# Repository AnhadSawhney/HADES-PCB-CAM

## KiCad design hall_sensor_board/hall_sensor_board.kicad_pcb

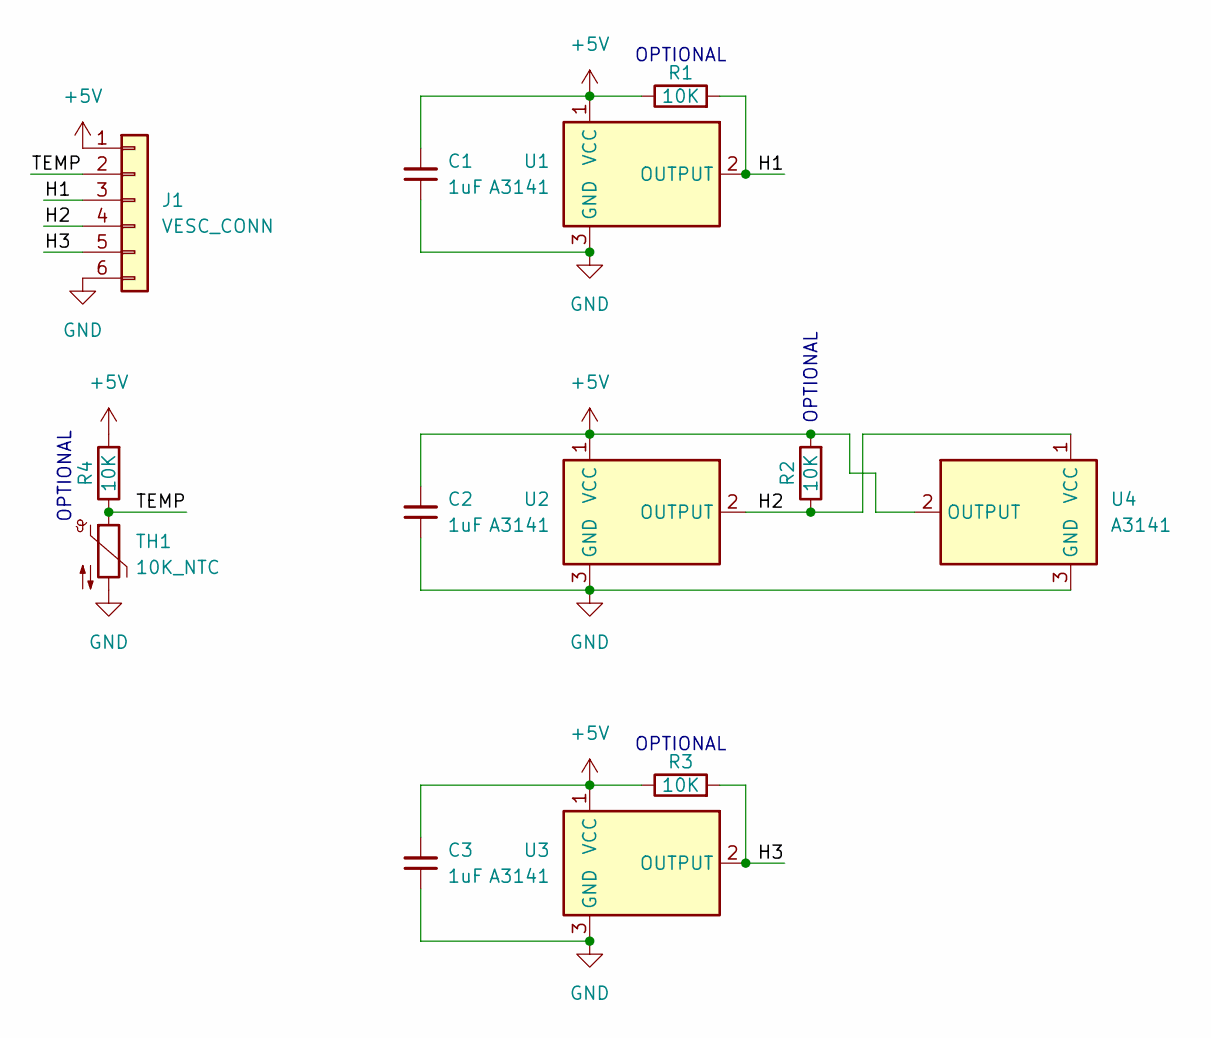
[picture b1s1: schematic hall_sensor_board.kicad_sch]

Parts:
C1, C2, C3: 1uF; C_0603_1608Metric
J1: VESC_CONN; PinHeader_1x06_P2.54mm_Vertical
R1, R2, R3, R4: 10K; R_0603_1608Metric
TH1: 10K_NTC; R_0603_1608Metric
U1, U2, U3, U4: A3141; SOT-23

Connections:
+5V: C1.2, C2.2, C3.2, J1.1, R1.1, R2.2, R3.1, R4.2, U1.1 (VCC), U2.1 (VCC), U3.1 (VCC), U4.2 (OUTPUT)
/H1: J1.3, R1.2, U1.2 (OUTPUT)
/H2: J1.4, R2.1, U2.2 (OUTPUT), U4.1 (VCC)
/H3: J1.5, R3.2, U3.2 (OUTPUT)
/TEMP: J1.2, R4.1, TH1.1
GND: C1.1, C2.1, C3.1, J1.6, TH1.2, U1.3 (GND), U2.3 (GND), U3.3 (GND), U4.3 (GND)

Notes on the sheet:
OPTIONAL

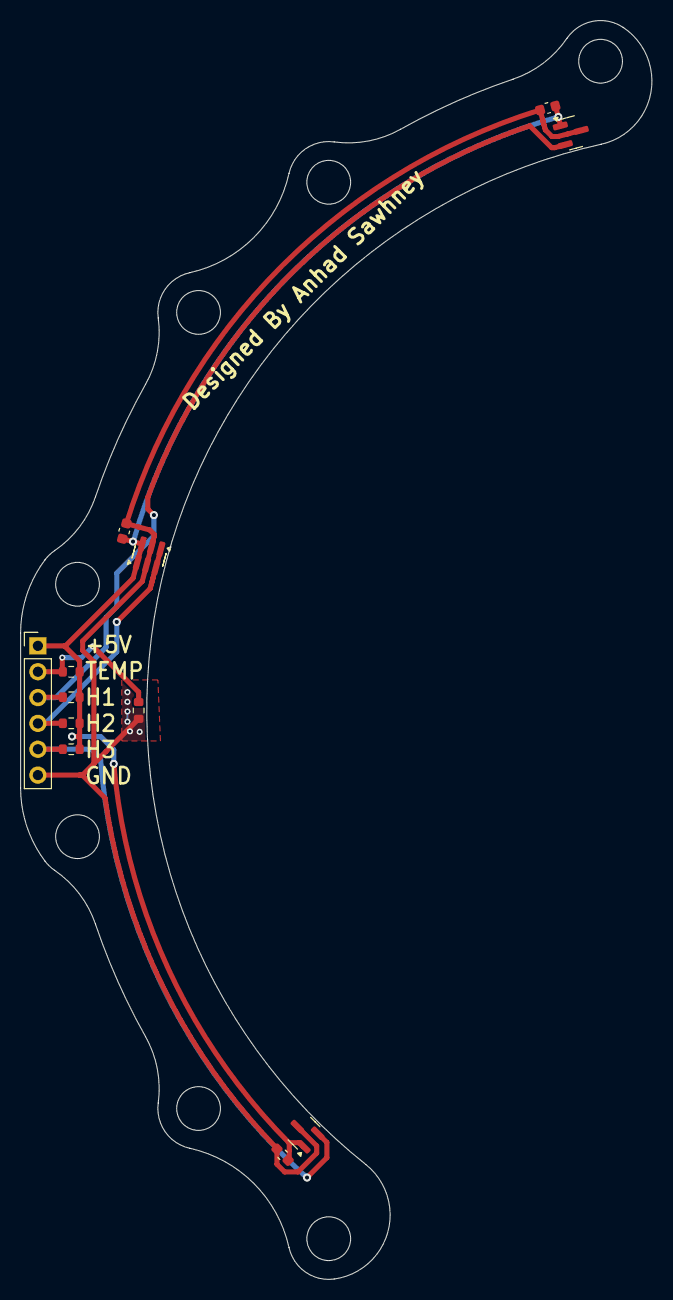
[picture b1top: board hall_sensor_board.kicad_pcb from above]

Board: 2 copper layers, 62.0 x 123.7 mm, 13 parts (0 on the bottom side), 6 nets.

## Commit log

2025-01-14 add dxfs
2025-01-15 Create Top Board
2025-01-15 add mid board
2025-02-15 ares pulley
2025-02-18 cam for kratos top hub
2025-02-19 Added Bottom Weapon Hub CAM
2025-02-19 Updating Feeds and Speeds
2025-02-22 attempt at shaft cam
2025-02-22 UpdatedShaft
2025-02-22 cammed rotor top
2025-02-24 pcbs sent to pcbway
2025-03-01 Updated references in assembly
2025-03-02 bottom hub improvements
2025-03-05 Updated Feeds and Speeds for All Operations
2025-03-08 midplate
2025-03-08 Added Center Hub CAM
    I created the CAM for the center hub; it just needs feeds and speed
2025-03-08 center chunk and weapon top hub
2025-03-08 Added 2024 Version of Center Hub
    2024 Version of the CAM for the center hub
2025-03-08 Modified Center Hub CAM
2025-03-09 Renamed Some Things for Standardization
2025-03-19 center hub update
2025-03-19 bottom weapon hub updates
2025-04-01 motor shaft
2025-04-12 Added billet chassis folder
2025-04-20 hall sensor board
